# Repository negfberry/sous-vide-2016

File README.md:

# sous-vide-2016
Sous vide Arduino shield software &amp; hardware

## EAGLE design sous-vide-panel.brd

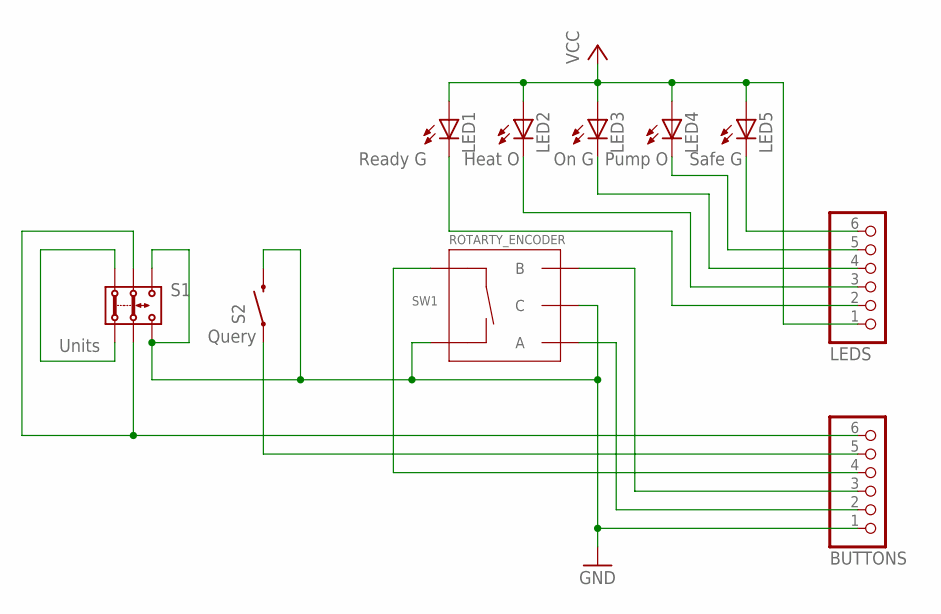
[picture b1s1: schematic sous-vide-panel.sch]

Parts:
BUTTONS: PINHD-1X6; 1X06
LED1: Ready G; LED5MM
LED2: Heat O; LED5MM
LED3: On G; LED5MM
LED4: Pump O; LED5MM
LED5: Safe G; LED5MM
LEDS: PINHD-1X6; 1X06
S1: Units; 2P2T
S2: Query; TACTILE-PTH-12MM
SW1: ROTARTY_ENCODER; ROTARY_ENC_PLAIN

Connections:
GND: BUTTONS.1, S1.3.1, S1.3.2, S2.3 (2), SW1.C, SW1.SW-
unnamed: BUTTONS.6, S1.2.1, S1.2.2
unnamed: BUTTONS.5, S2.1
unnamed: BUTTONS.4, SW1.SW+
unnamed: BUTTONS.3, SW1.B
unnamed: LED5.K (C), LEDS.6
unnamed: LED4.K (C), LEDS.5
unnamed: BUTTONS.2, SW1.A
unnamed: LED3.K (C), LEDS.4
unnamed: LED2.K (C), LEDS.3
unnamed: LED1.K (C), LEDS.2
unnamed: S1.1.1, S1.1.2
VCC: LED1.A, LED2.A, LED3.A, LED4.A, LED5.A, LEDS.1

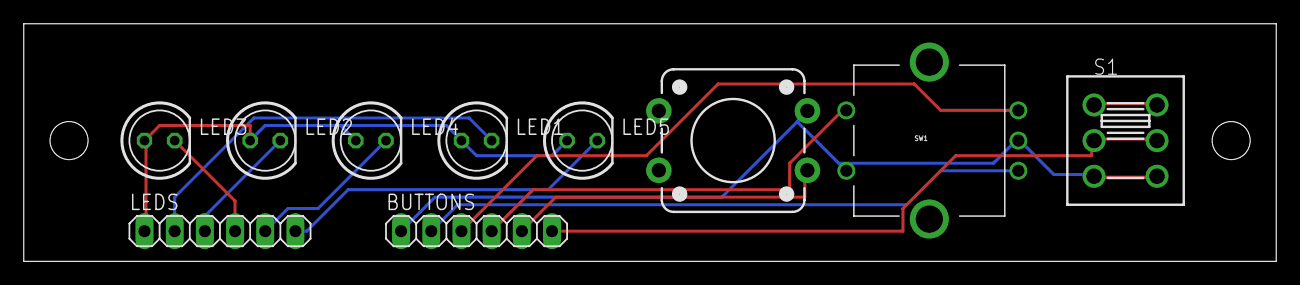
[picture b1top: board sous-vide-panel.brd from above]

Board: 2 copper layers, 105.4 x 20.0 mm, 10 parts (0 on the bottom side), 13 nets.

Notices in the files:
parts and their libraries:
SparkFun-Electromechanical: Licensing: Creative Commons ShareAlike 4.0 International - https://creativecommons.org/licenses/by-sa/4.0
